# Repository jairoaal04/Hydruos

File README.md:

# Hydruos
Mechatronic degree project.

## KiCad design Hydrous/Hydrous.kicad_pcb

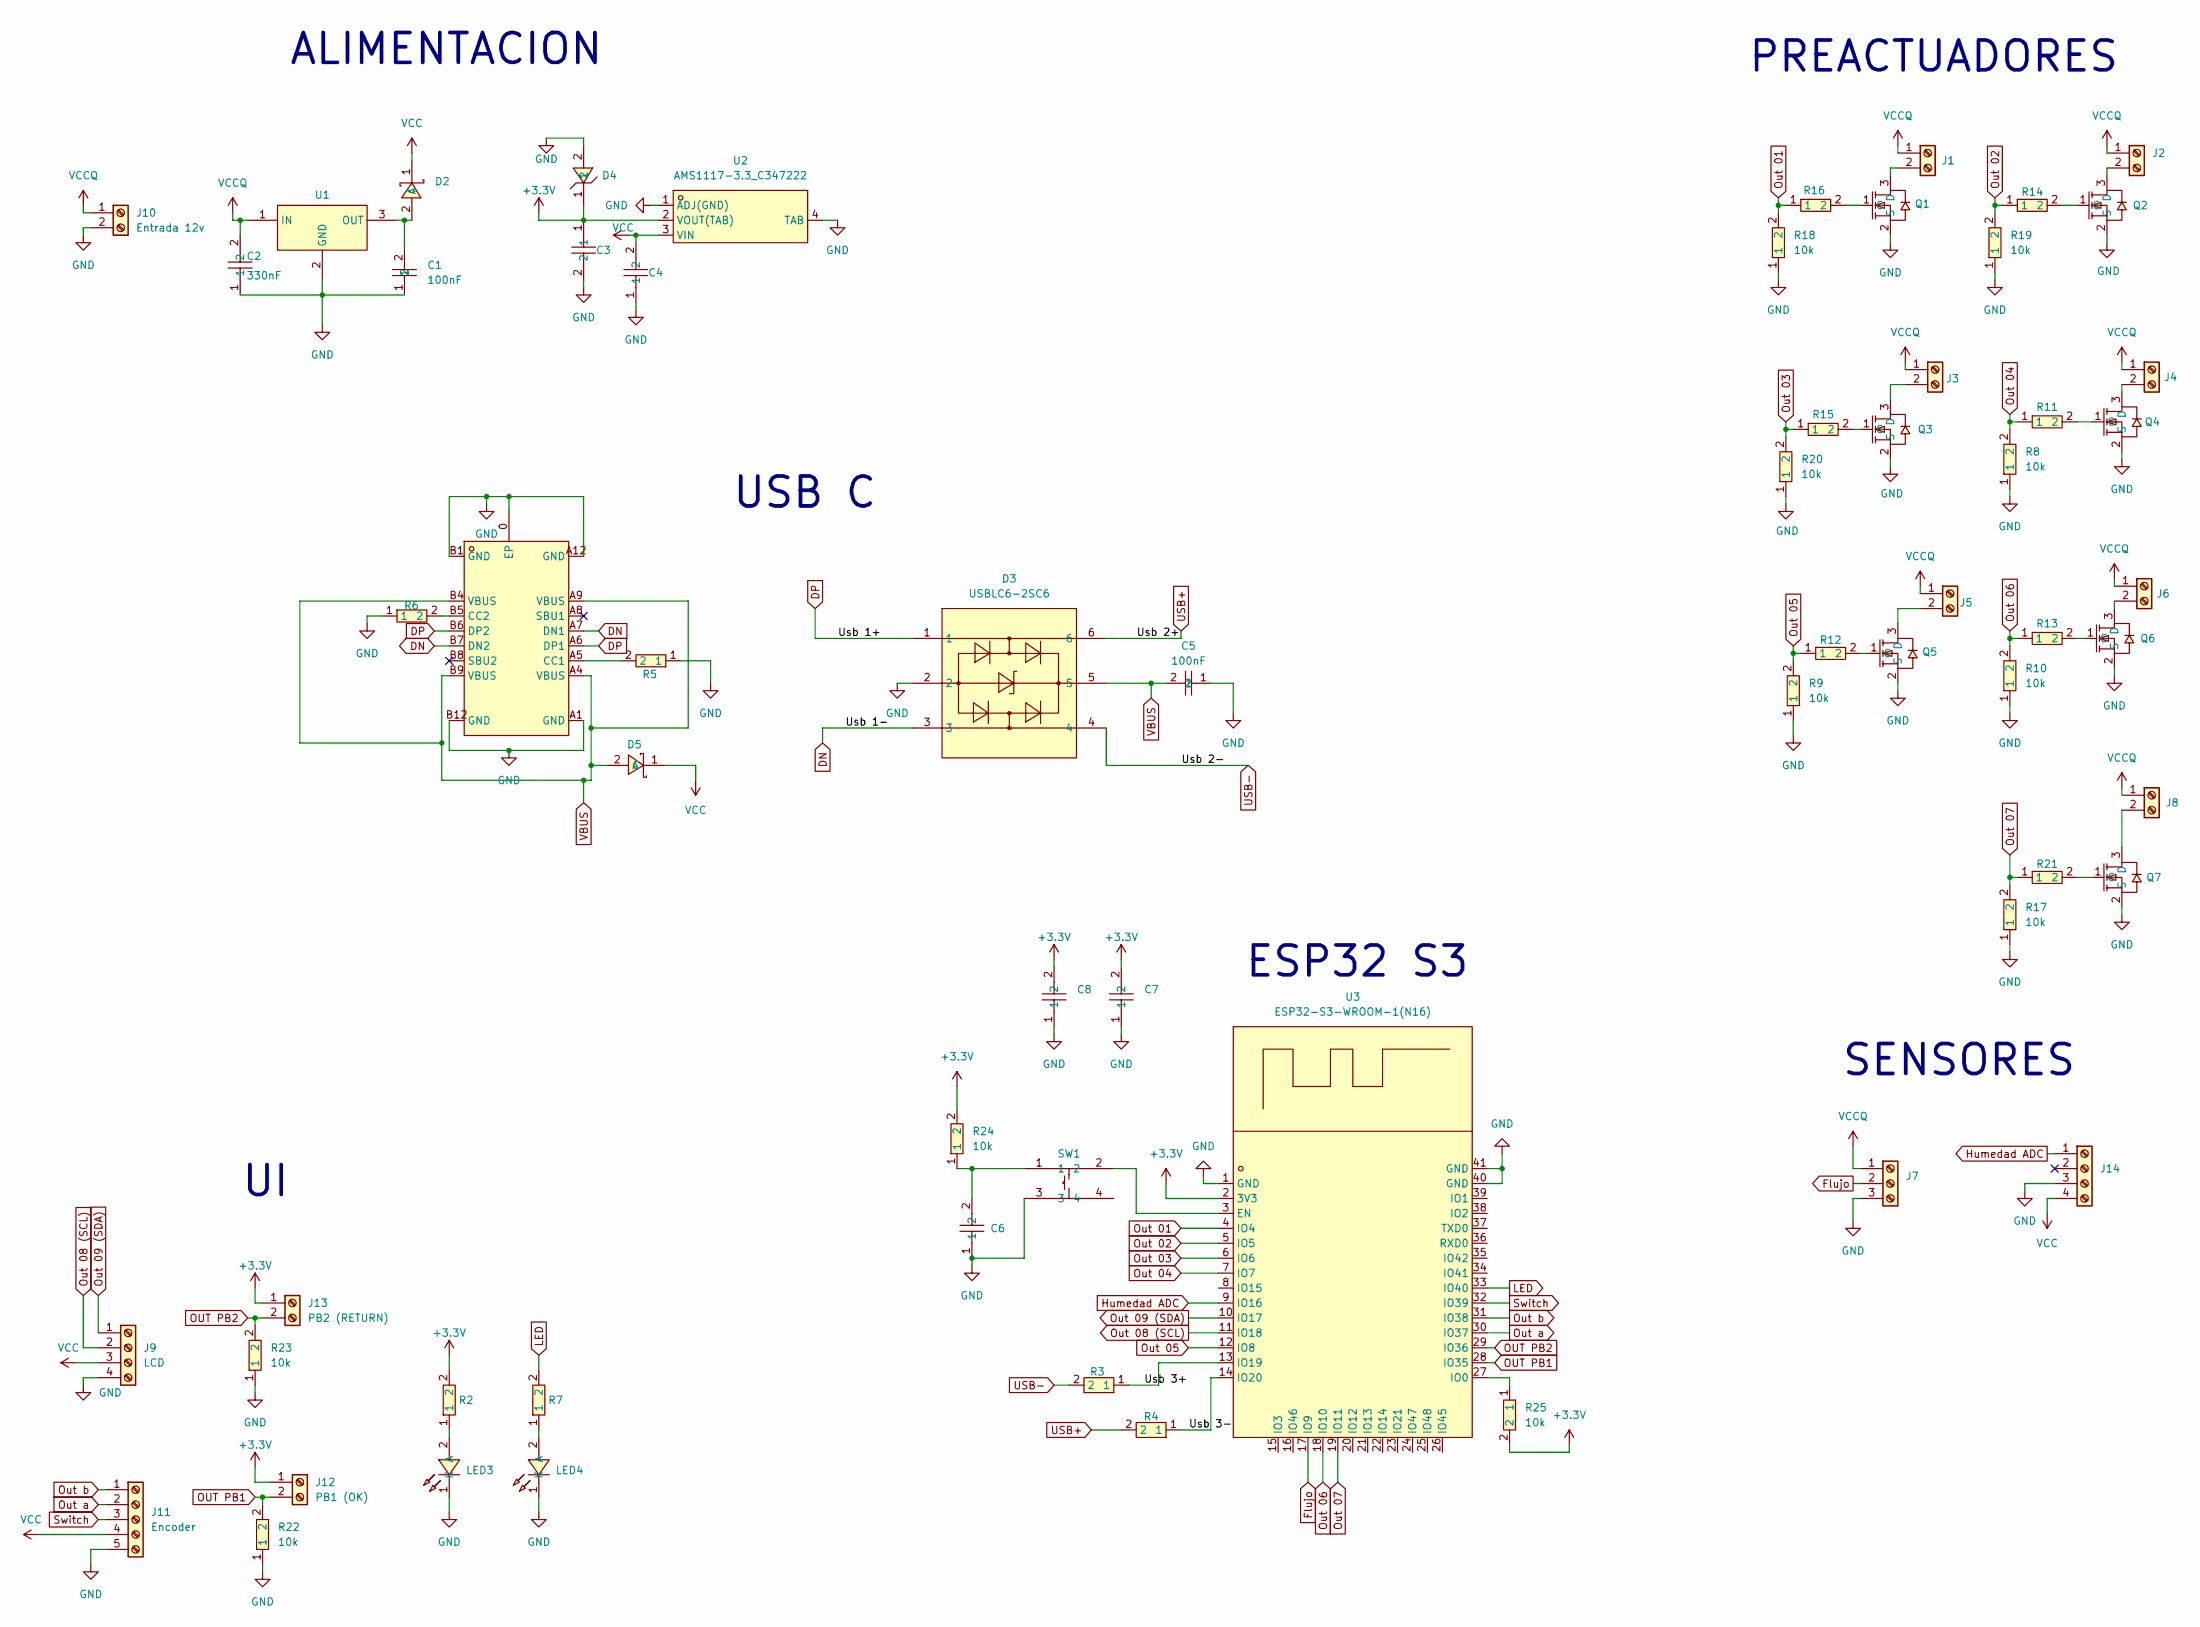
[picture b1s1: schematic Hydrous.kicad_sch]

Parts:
C1, C5: 100nF; C1206; LCSC Part C13585
C2: 330nF; C1206; LCSC Part C192444
C3: CS3216X5R226K160NRI; C1206; LCSC Part C513771
C4: CS3216X5R106K500NRI; C1206; LCSC Part C513774
C6: CL31B105KBHNNNE; C1206; LCSC Part C1848
C7: CC0805KRX7R9BB104; C0805; LCSC Part C49678
C8: CS2012X7R105K500NRE; C0805; LCSC Part C516002
D2, D5: SS520_C466507; SMA_L4.4-W2.8-LS5.4-RD; LCSC Part C466507
D3: USBLC6-2SC6; SOT-23-6_L2.9-W1.6-P0.95-LS2.8-BL; LCSC Part C7519
D4: SMF3.3A; SOD-123_L2.8-W1.8-LS3.7-RD; LCSC Part C283866
J1, J2, J3, J4, J5, J6: Screw_Terminal_01x02; CONN-TH_2P-P5.00_CPC3703CTR; LCSC Part C3703
J7: Sensor de flujo; CONN-TH_3P-P5.00_WJ128V-5.0-3P; LCSC Part C8270
J8: Dispensador de nutrientes; CONN-TH_2P-P5.00_CPC3703CTR; LCSC Part C3703
J9: LCD; CONN-TH_4P-P3.81_KF124-3.81-4P; LCSC Part C69809
J10: Entrada 12v; CONN-TH_2P-P5.00_CPC3703CTR; LCSC Part C3703
J11: Encoder; CONN-TH_5P-P3.81_KF124-3.81-5P; LCSC Part C72336
J12: PB1 (OK); CONN-TH_2P-P5.00_CPC3703CTR; LCSC Part C3703
J13: PB2 (RETURN); CONN-TH_2P-P5.00_CPC3703CTR; LCSC Part C3703
J14: Sensor de humedad; CONN-TH_4P-P3.81_KF124-3.81-4P; LCSC Part C69809
LED3, LED4: XL-2012SURC; LED0805-RD_RED; LCSC Part C965812
Q1, Q2, Q3, Q4, Q5, Q6, Q7: AO3400_C4748804; SOT-23_L2.9-W1.3-P1.90-LS2.4-BR; LCSC Part C4748804
R2, R7: RC0805FR-0775RL; R0805; LCSC Part C141697
R3, R4: FRC1206F33R0TS; R1206; LCSC Part C2907384
R5, R6: 1206W4F5101T5E; R1206; LCSC Part C26033
R8, R9, R10, R17, R18, R19, R20, R22, R23, R24, R25: 10k; R1206; LCSC Part C132649
R11, R12, R13, R14, R15, R16, R21: RC1206FR-07150RL; R1206; LCSC Part C137387
SW1: SKRPACE010; KEY-SMD_4P-L4.2-W3.2-P2.20-LS4.6; LCSC Part C139797
U1: L7805ABD2T-TR; TO-263-2_L10.0-W9.2-P5.08-LS15.3-TL-CW; LCSC Part C86206
U2: AMS1117-3.3_C347222; SOT-223-4_L6.5-W3.5-P2.30-LS7.0-BR; LCSC Part C347222
U3: ESP32-S3-WROOM-1(N16); WIRELM-SMD_ESP32-S3-WROOM-1; LCSC Part C2913199
USB1: TYPE-C-31-M-13; USB-C-SMD_TYPE-C-31-M-13; LCSC Part C223906

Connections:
+3.3V: C3.1, C7.2, C8.2, D4.1, J12.1, J13.1, R2.2, R24.2, R25.2, U2.2 (VOUT(TAB)), U3.2 (3V3)
/Usb 3+: R3.1, U3.13 (IO19)
/Usb 3-: R4.1, U3.14 (IO20)
DN: D3.3, USB1.A7 (DN1), USB1.B7 (DN2)
DP: D3.1, USB1.A6 (DP1), USB1.B6 (DP2)
Flujo: J7.2, U3.17 (IO9)
GND: C1.1, C2.1, C3.2, C4.1, C5.1, C6.1, C7.1, C8.1, D3.2, D4.2, J7.3, J9.4, J10.2, J11.5, J14.3, LED3.1 (K), LED4.1 (K), Q1.2 (S), Q2.2 (S), Q3.2 (S), Q4.2 (S), Q5.2 (S), Q6.2 (S), Q7.2 (S), R5.1, R6.1, R8.1, R9.1, R10.1, R17.1, R18.1, R19.1, R20.1, R22.1, R23.1, SW1.3, U1.2 (GND), U2.1 (ADJ(GND)), U2.4 (TAB), U3.1 (GND), U3.40 (GND), U3.41 (GND), USB1.0 (EP), USB1.A1 (GND), USB1.A12 (GND), USB1.B1 (GND), USB1.B12 (GND)
Humedad ADC: J14.1, U3.9 (IO16)
LED: R7.2, U3.33 (IO40)
unnamed: C6.2, R24.1, SW1.1
unnamed: C1.2, D2.2 (A), U1.3 (OUT)
unnamed: J1.2, Q1.3 (D)
unnamed: J2.2, Q2.3 (D)
unnamed: J3.2, Q3.3 (D)
unnamed: J4.2, Q4.3 (D)
unnamed: J5.2, Q5.3 (D)
unnamed: J6.2, Q6.3 (D)
unnamed: J8.2, Q7.3 (D)
unnamed: LED3.2 (A), R2.1
unnamed: LED4.2 (A), R7.1
unnamed: Q1.1 (G), R16.2
unnamed: Q2.1 (G), R14.2
unnamed: Q3.1 (G), R15.2
unnamed: Q4.1 (G), R11.2
unnamed: Q5.1 (G), R12.2
unnamed: Q6.1 (G), R13.2
unnamed: Q7.1 (G), R21.2
unnamed: SW1.2, U3.3 (EN)
unnamed: R25.1, U3.27 (IO0)
unnamed: R5.2, USB1.A5 (CC1)
unnamed: R6.2, USB1.B5 (CC2)
OUT PB1: J12.2, R22.2, U3.28 (IO35)
OUT PB2: J13.2, R23.2, U3.29 (IO36)
Out 01: R16.1, R18.2, U3.4 (IO4)
Out 02: R14.1, R19.2, U3.5 (IO5)
Out 03: R15.1, R20.2, U3.6 (IO6)
Out 04: R8.2, R11.1, U3.7 (IO7)
Out 05: R9.2, R12.1, U3.12 (IO8)
Out 06: R10.2, R13.1, U3.18 (IO10)
Out 07: R17.2, R21.1, U3.19 (IO11)
Out 08 (SCL): J9.2, U3.11 (IO18)
Out 09 (SDA): J9.1, U3.10 (IO17)
Out a: J11.2, U3.30 (IO37)
Out b: J11.1, U3.31 (IO38)
Switch: J11.3, U3.32 (IO39)
USB+: D3.6, R4.2
USB-: D3.4, R3.2
VBUS: C5.2, D3.5, D5.2 (A), USB1.A4 (VBUS), USB1.A9 (VBUS), USB1.B4 (VBUS), USB1.B9 (VBUS)
VCC: C4.2, D2.1 (C), D5.1 (C), J9.3, J11.4, J14.4, U2.3 (VIN)
VCCQ: C2.2, J1.1, J2.1, J3.1, J4.1, J5.1, J6.1, J7.1, J8.1, J10.1, U1.1 (IN)

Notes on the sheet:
SENSORES
ALIMENTACION
ESP32 S3
PREACTUADORES
USB C

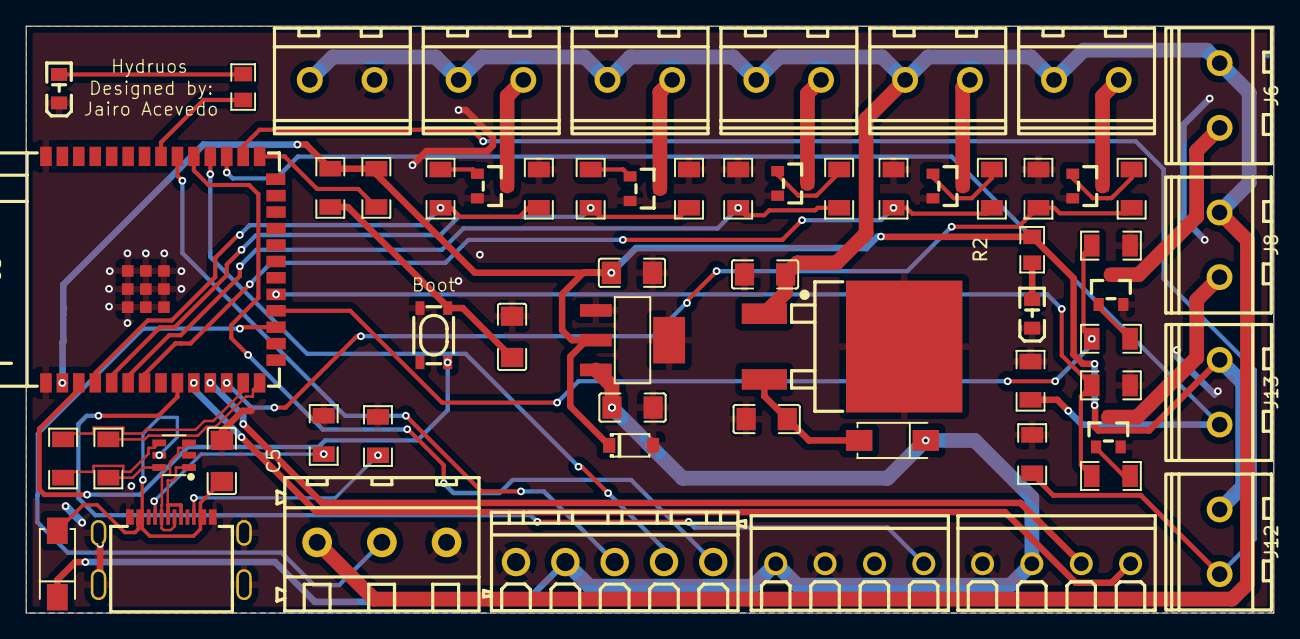
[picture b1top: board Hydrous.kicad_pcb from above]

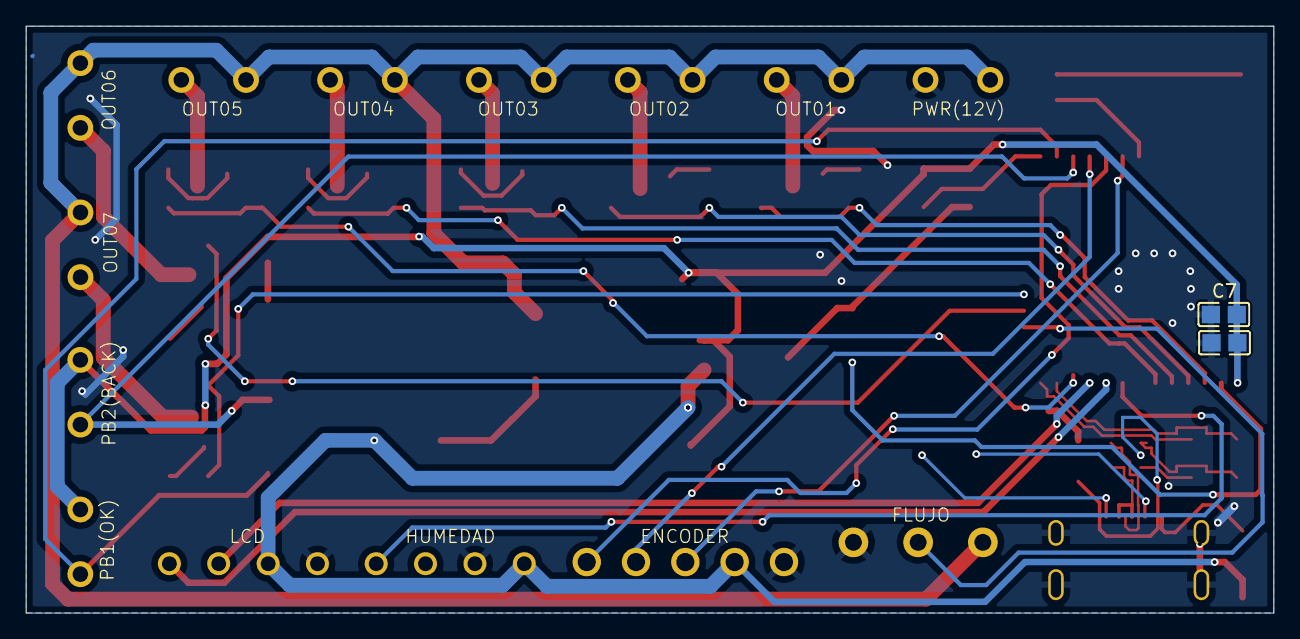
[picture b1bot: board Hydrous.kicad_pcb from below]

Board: 2 copper layers, 96.4 x 45.3 mm, 64 parts (2 on the bottom side), 50 nets.

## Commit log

2025-03-26 Gerber update
